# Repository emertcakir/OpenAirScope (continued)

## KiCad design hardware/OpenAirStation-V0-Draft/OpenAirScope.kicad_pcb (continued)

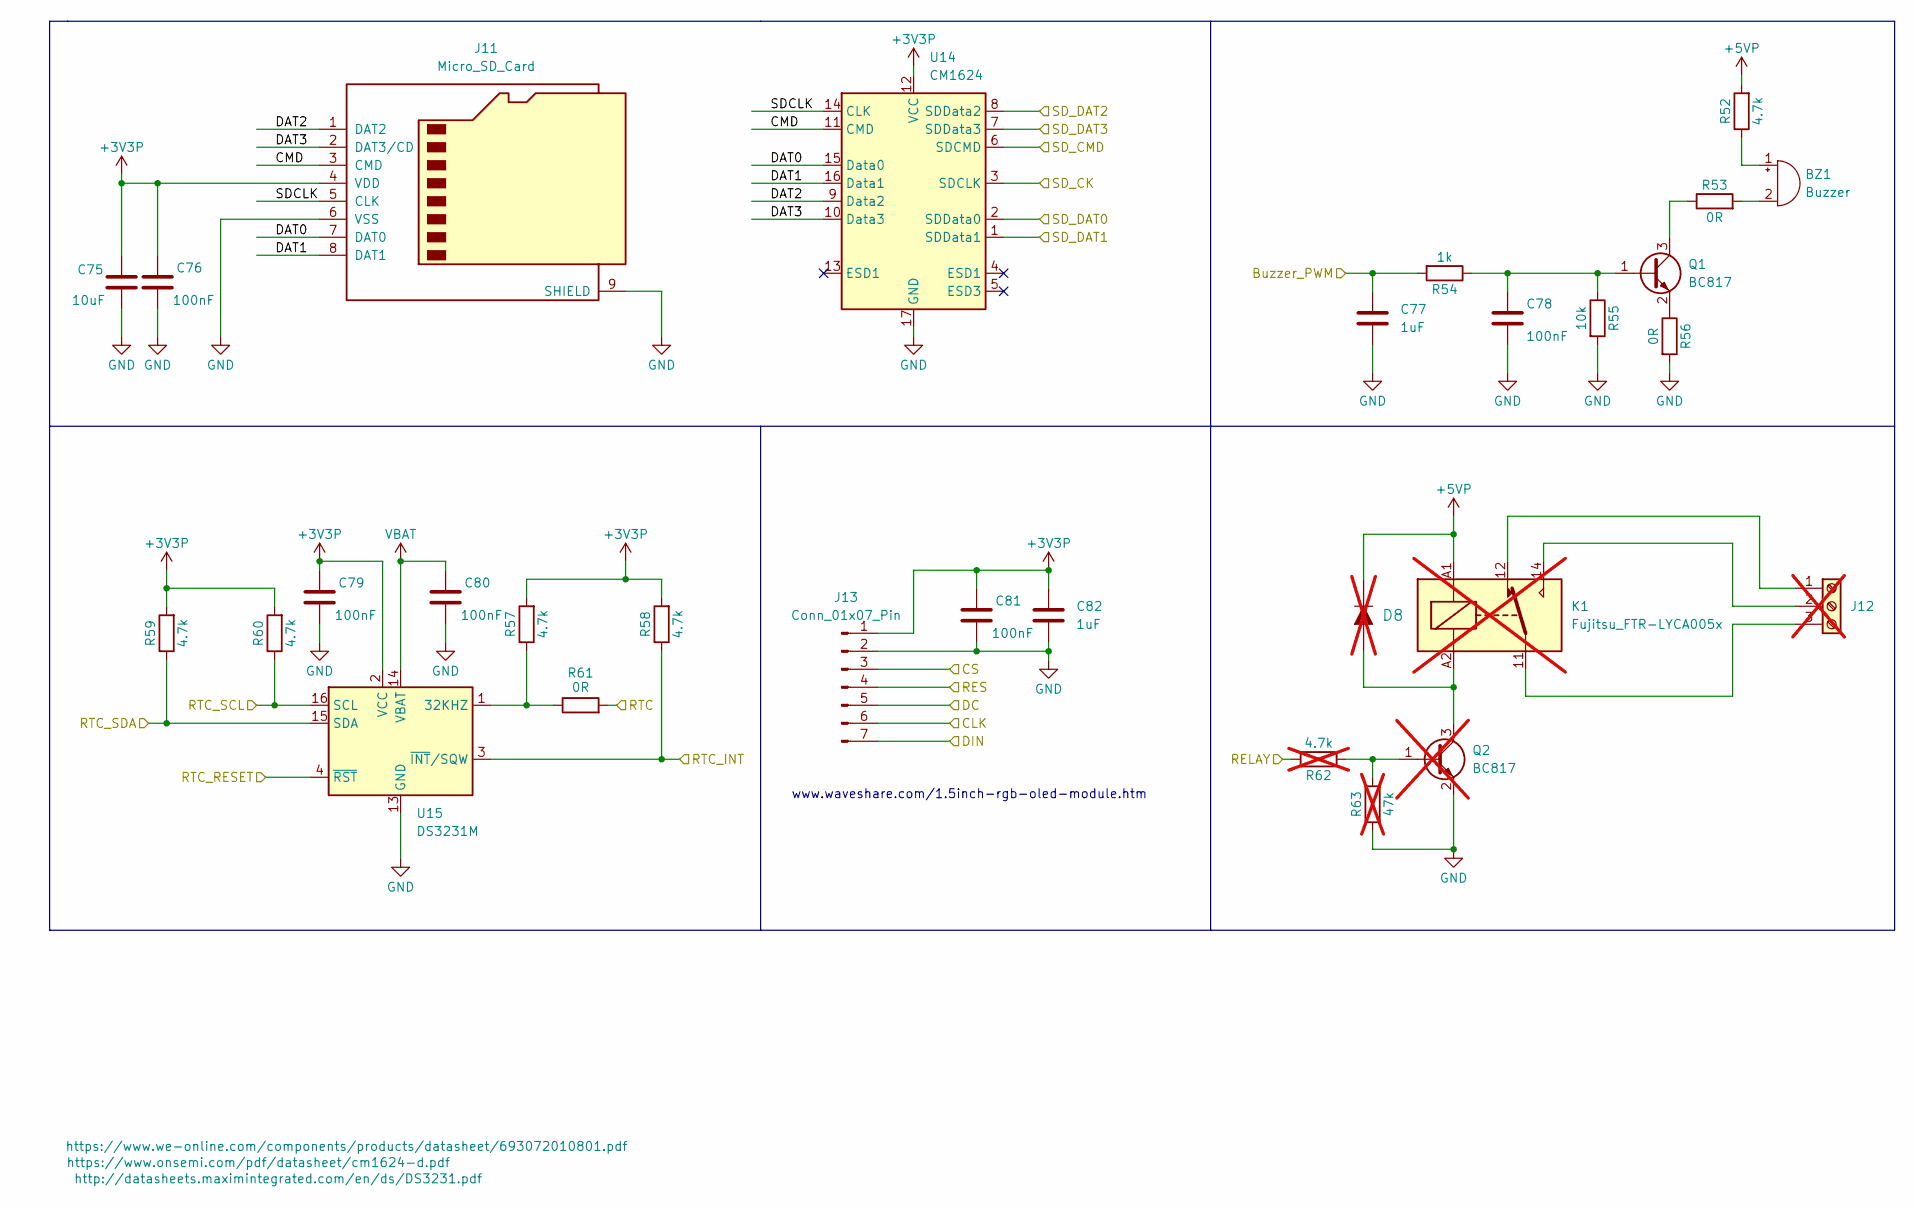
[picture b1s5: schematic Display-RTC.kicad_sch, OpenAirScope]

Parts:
BZ1: Buzzer; MagneticBuzzer_ProSignal_ABT-410-RC
C75: 10uF; C_0603_1608Metric
C76, C78, C79, C80, C81: 100nF; C_0603_1608Metric
C77, C82: 1uF; C_1206_3216Metric
D8: 1N4148W-TP; SOD-123; MPN 1N4148W-TP; Digi-Key_PN 1N4148WTPMSCT-ND; not fitted
J11: Micro_SD_Card; microSD_HC_Wuerth_693072010801
J12: Screw_Terminal_01x03; TerminalBlock_MetzConnect_Type059_RT06303HBWC_1x03_P3.50mm_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; not fitted
J13: Conn_01x07_Pin; PinHeader_1x07_P2.54mm_Vertical
K1: Fujitsu_FTR-LYCA005x; Relay_SPDT_Fujitsu_FTR-LYCA005x_FormC_Vertical; not fitted
Q1: BC817; SOT-23
Q2: BC817; SOT-23; not fitted
R52, R57, R58, R59, R60: 4.7k; R_0603_1608Metric
R53, R56, R61: 0R; R_0603_1608Metric
R54: 1k; R_0603_1608Metric
R55: 10k; R_0603_1608Metric
R62: 4.7k; R_0603_1608Metric; not fitted
R63: 47k; R_0603_1608Metric; not fitted
U14: CM1624; OnSemi_UDFN-16-1EP_1.35x3.3mm_P0.4mm_EP0.4x2.8mm
U15: DS3231M; SOIC-16W_7.5x10.3mm_P1.27mm

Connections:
+3V3P: C75.1, C76.1, C79.1, C81.1, C82.1, J11.4 (VDD), J13.1, R57.2, R58.2, R59.2, R60.2, U14.12 (VCC), U15.2 (VCC); also elsewhere on the board
+5VP: D8.K, K1.A1, R52.2; also elsewhere on the board
/Display-RTC/Buzzer_PWM: C77.1, R54.2; also elsewhere on the board
/Display-RTC/CLK: J13.6; also elsewhere on the board
/Display-RTC/CMD: J11.3 (CMD), U14.11 (CMD)
/Display-RTC/CS: J13.3; also elsewhere on the board
/Display-RTC/DAT0: J11.7 (DAT0), U14.15 (Data0)
/Display-RTC/DAT1: J11.8 (DAT1), U14.16 (Data1)
/Display-RTC/DAT2: J11.1 (DAT2), U14.9 (Data2)
/Display-RTC/DAT3: J11.2 (DAT3/CD), U14.10 (Data3)
/Display-RTC/DC: J13.5; also elsewhere on the board
/Display-RTC/DIN: J13.7; also elsewhere on the board
/Display-RTC/RES: J13.4; also elsewhere on the board
/Display-RTC/RTC: R61.2; also elsewhere on the board
/Display-RTC/RTC_INT: R58.1, U15.3 (~INT/SQW); also elsewhere on the board
/Display-RTC/RTC_RESET: U15.4 (~RST); also elsewhere on the board
/Display-RTC/RTC_SCL: R60.1, U15.16 (SCL); also elsewhere on the board
/Display-RTC/RTC_SDA: R59.1, U15.15 (SDA); also elsewhere on the board
/Display-RTC/SDCLK: J11.5 (CLK), U14.14 (CLK)
/Display-RTC/SD_CK: U14.3 (SDCLK); also elsewhere on the board
/Display-RTC/SD_CMD: U14.6 (SDCMD); also elsewhere on the board
/Display-RTC/SD_DAT0: U14.2 (SDData0); also elsewhere on the board
/Display-RTC/SD_DAT1: U14.1 (SDData1); also elsewhere on the board
/Display-RTC/SD_DAT2: U14.8 (SDData2); also elsewhere on the board
/Display-RTC/SD_DAT3: U14.7 (SDData3); also elsewhere on the board
GND: C75.2, C76.2, C77.2, C78.2, C79.2, C80.2, C81.2, C82.2, J11.6 (VSS), J11.9 (SHIELD), J13.2, Q2.2 (E), R55.2, R56.2, R63.1, U14.17 (GND), U15.5 (GND), U15.6 (GND), U15.7 (GND), U15.8 (GND), U15.9 (GND), U15.10 (GND), U15.11 (GND), U15.12 (GND), U15.13 (GND); also elsewhere on the board
unnamed: BZ1.1 (+), R52.1
unnamed: BZ1.2 (-), R53.2
unnamed: D8.A, K1.A2, Q2.3 (C)
unnamed: J12.1, K1.12
unnamed: J12.2, K1.14
unnamed: J12.3, K1.11
unnamed: C78.1, Q1.1 (B), R54.1, R55.1
unnamed: Q1.3 (C), R53.1
unnamed: Q1.2 (E), R56.1
unnamed: Q2.1 (B), R62.1, R63.2
unnamed: R57.1, R61.1, U15.1 (32KHZ)
VBAT: C80.1, U15.14 (VBAT); also elsewhere on the board

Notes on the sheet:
www.waveshare.com/1.5inch-rgb-oled-module.htm

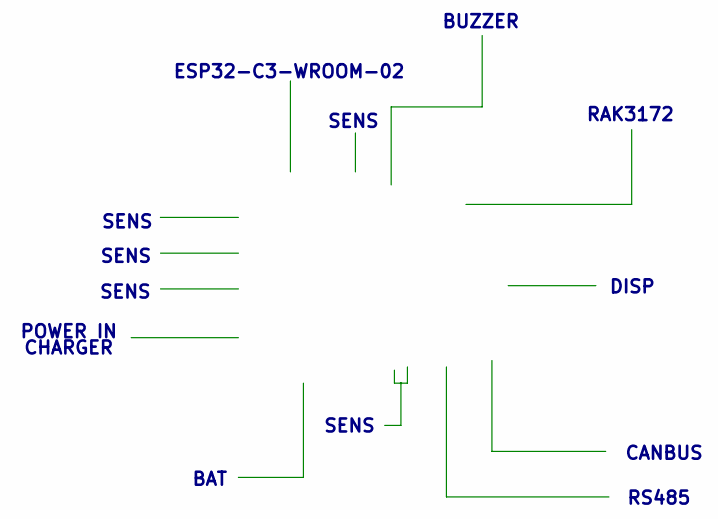
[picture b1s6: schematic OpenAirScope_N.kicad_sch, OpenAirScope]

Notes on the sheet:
CHARGER
DISP
SENS
BAT
ESP32-C3-WROOM-02
RAK3172
RS485
CANBUS
POWER IN
BUZZER

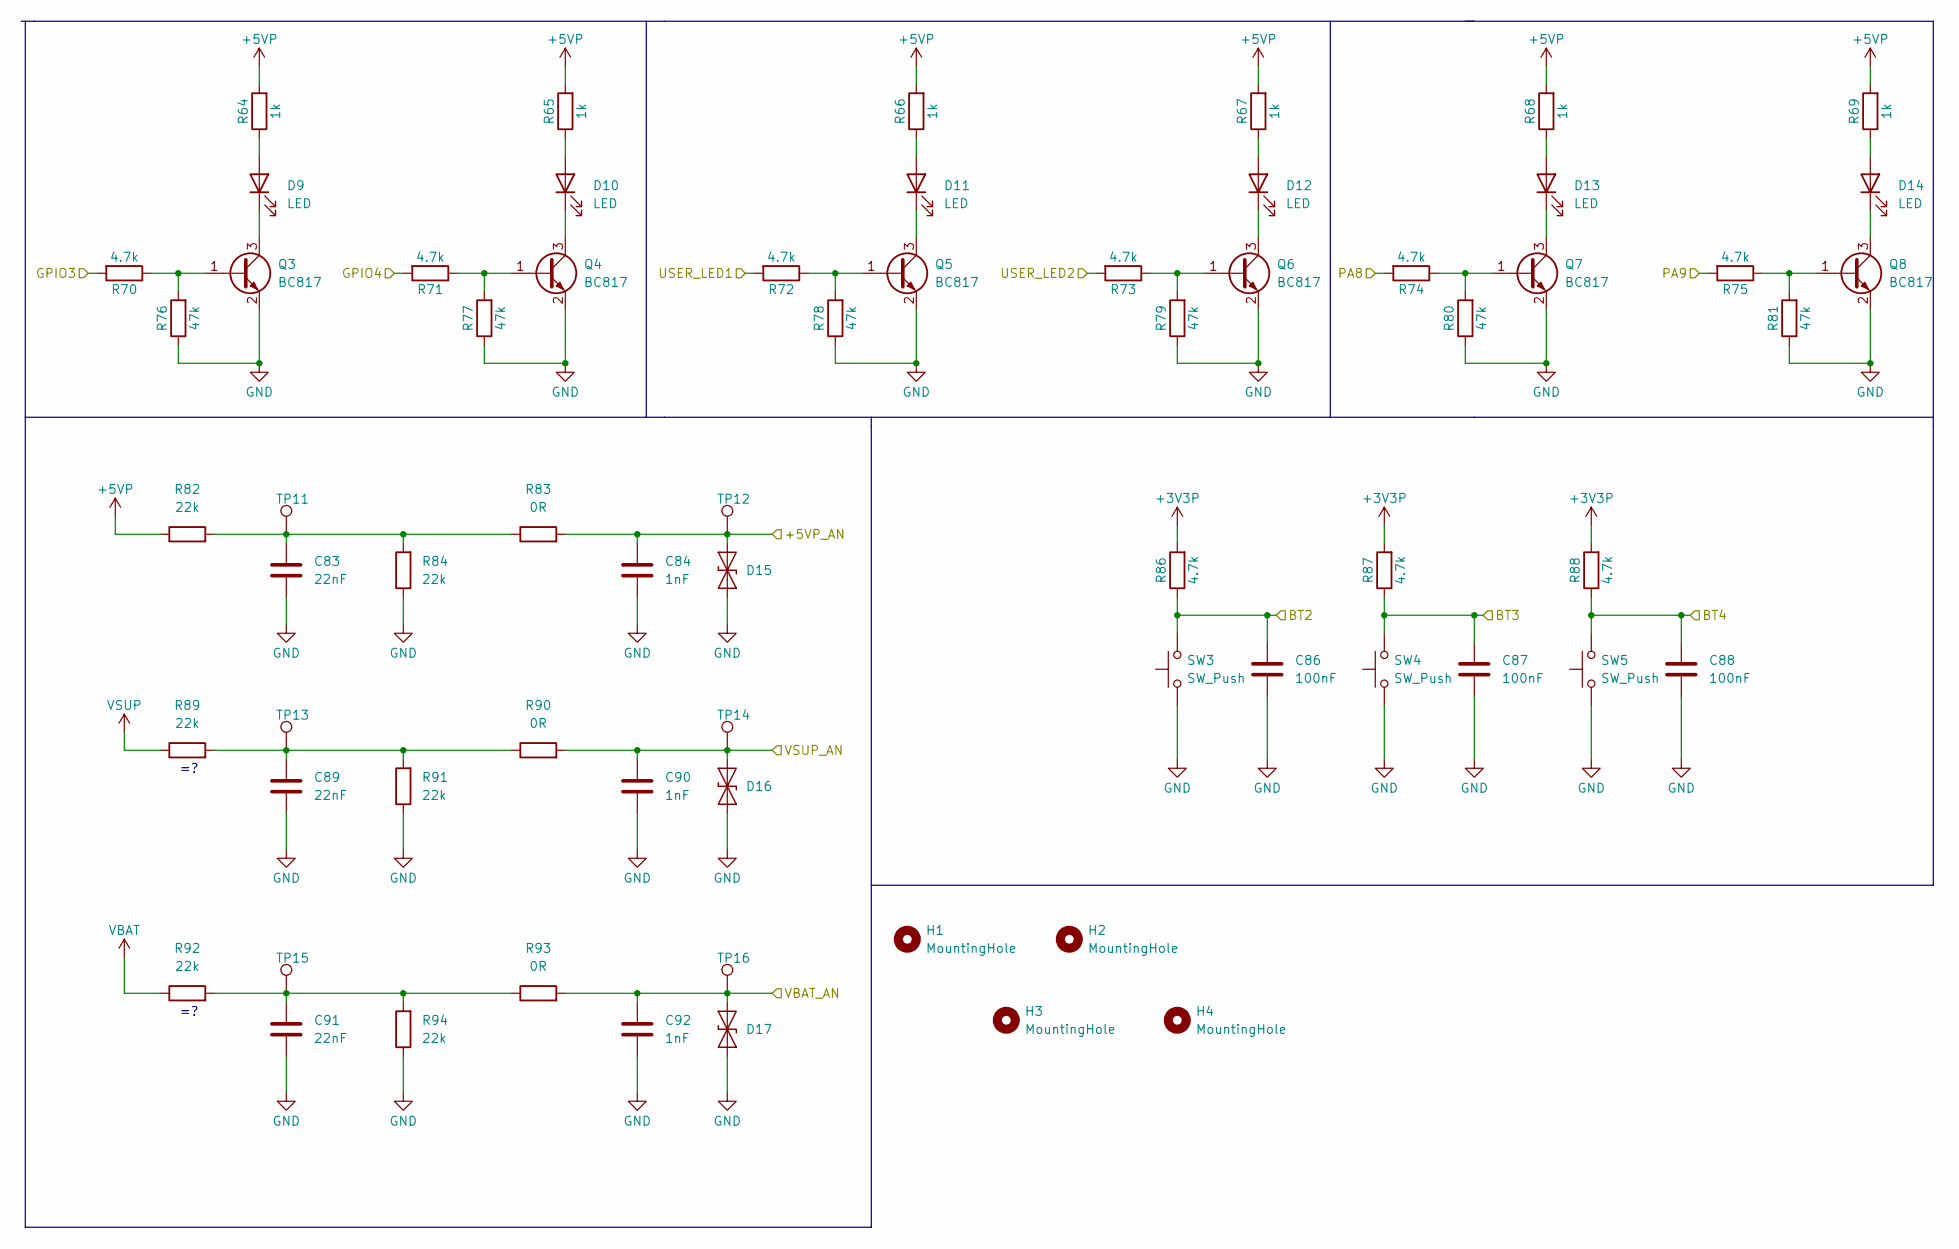
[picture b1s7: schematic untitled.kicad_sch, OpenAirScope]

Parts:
C83, C89, C91: 22nF; C_0603_1608Metric
C84, C90, C92: 1nF; C_0603_1608Metric
C86, C87, C88: 100nF; C_0603_1608Metric
D9, D10, D11, D12, D13, D14: LED; LED_0603_1608Metric
D15, D16, D17: ESD9B3.3ST5G; D_SOD-923
H1, H2, H3, H4: MountingHole; MountingHole_3.2mm_M3_ISO7380
Q3, Q4, Q5, Q6, Q7, Q8: BC817; SOT-23
R64, R65, R66, R67, R68, R69: 1k; R_0603_1608Metric
R70, R71, R72, R73, R74, R75, R86, R87, R88: 4.7k; R_0603_1608Metric
R76, R77, R78, R79, R80, R81: 47k; R_0603_1608Metric
R82, R84, R89, R91, R92, R94: 22k; R_0603_1608Metric
R83, R90, R93: 0R; R_0603_1608Metric
SW3, SW4, SW5: SW_Push; SW_PUSH_6mm_H13mm
TP11, TP12, TP13, TP14, TP15, TP16: TestPoint; TestPoint_Pad_D1.0mm

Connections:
+3V3P: R86.2, R87.2, R88.2; also elsewhere on the board
+5VP: R64.2, R65.2, R66.2, R67.2, R68.2, R69.2, R82.1; also elsewhere on the board
/Conn/GPIO3: R70.2; also elsewhere on the board
/Conn/GPIO4: R71.2; also elsewhere on the board
/Conn/PA8: R74.2; also elsewhere on the board
/Conn/PA9: R75.2; also elsewhere on the board
/Indicators/+5VP_AN: C84.1, D15.2 (A2), R83.2, TP12.1; also elsewhere on the board
/Indicators/BT2: C86.1, R86.1, SW3.2; also elsewhere on the board
/Indicators/BT3: C87.1, R87.1, SW4.2; also elsewhere on the board
/Indicators/BT4: C88.1, R88.1, SW5.2; also elsewhere on the board
/Indicators/USER_LED1: R72.2; also elsewhere on the board
/Indicators/USER_LED2: R73.2; also elsewhere on the board
/Indicators/VBAT_AN: C92.1, D17.2 (A2), R93.2, TP16.1; also elsewhere on the board
/Indicators/VSUP_AN: C90.1, D16.2 (A2), R90.2, TP14.1; also elsewhere on the board
GND: C83.2, C84.2, C86.2, C87.2, C88.2, C89.2, C90.2, C91.2, C92.2, D15.1 (A1), D16.1 (A1), D17.1 (A1), Q3.2 (E), Q4.2 (E), Q5.2 (E), Q6.2 (E), Q7.2 (E), Q8.2 (E), R76.1, R77.1, R78.1, R79.1, R80.1, R81.1, R84.1, R91.1, R94.1, SW3.1, SW4.1, SW5.1; also elsewhere on the board
unnamed: C83.1, R82.2, R83.1, R84.2, TP11.1
unnamed: C89.1, R89.2, R90.1, R91.2, TP13.1
unnamed: C91.1, R92.2, R93.1, R94.2, TP15.1
unnamed: D9.2 (A), R64.1
unnamed: D9.1 (K), Q3.3 (C)
unnamed: D10.2 (A), R65.1
unnamed: D10.1 (K), Q4.3 (C)
unnamed: D11.2 (A), R66.1
unnamed: D11.1 (K), Q5.3 (C)
unnamed: D12.2 (A), R67.1
unnamed: D12.1 (K), Q6.3 (C)
unnamed: D13.2 (A), R68.1
unnamed: D13.1 (K), Q7.3 (C)
unnamed: D14.2 (A), R69.1
unnamed: D14.1 (K), Q8.3 (C)
unnamed: Q3.1 (B), R70.1, R76.2
unnamed: Q4.1 (B), R71.1, R77.2
unnamed: Q5.1 (B), R72.1, R78.2
unnamed: Q6.1 (B), R73.1, R79.2
unnamed: Q7.1 (B), R74.1, R80.2
unnamed: Q8.1 (B), R75.1, R81.2
VBAT: R92.1; also elsewhere on the board
VSUP: R89.1; also elsewhere on the board

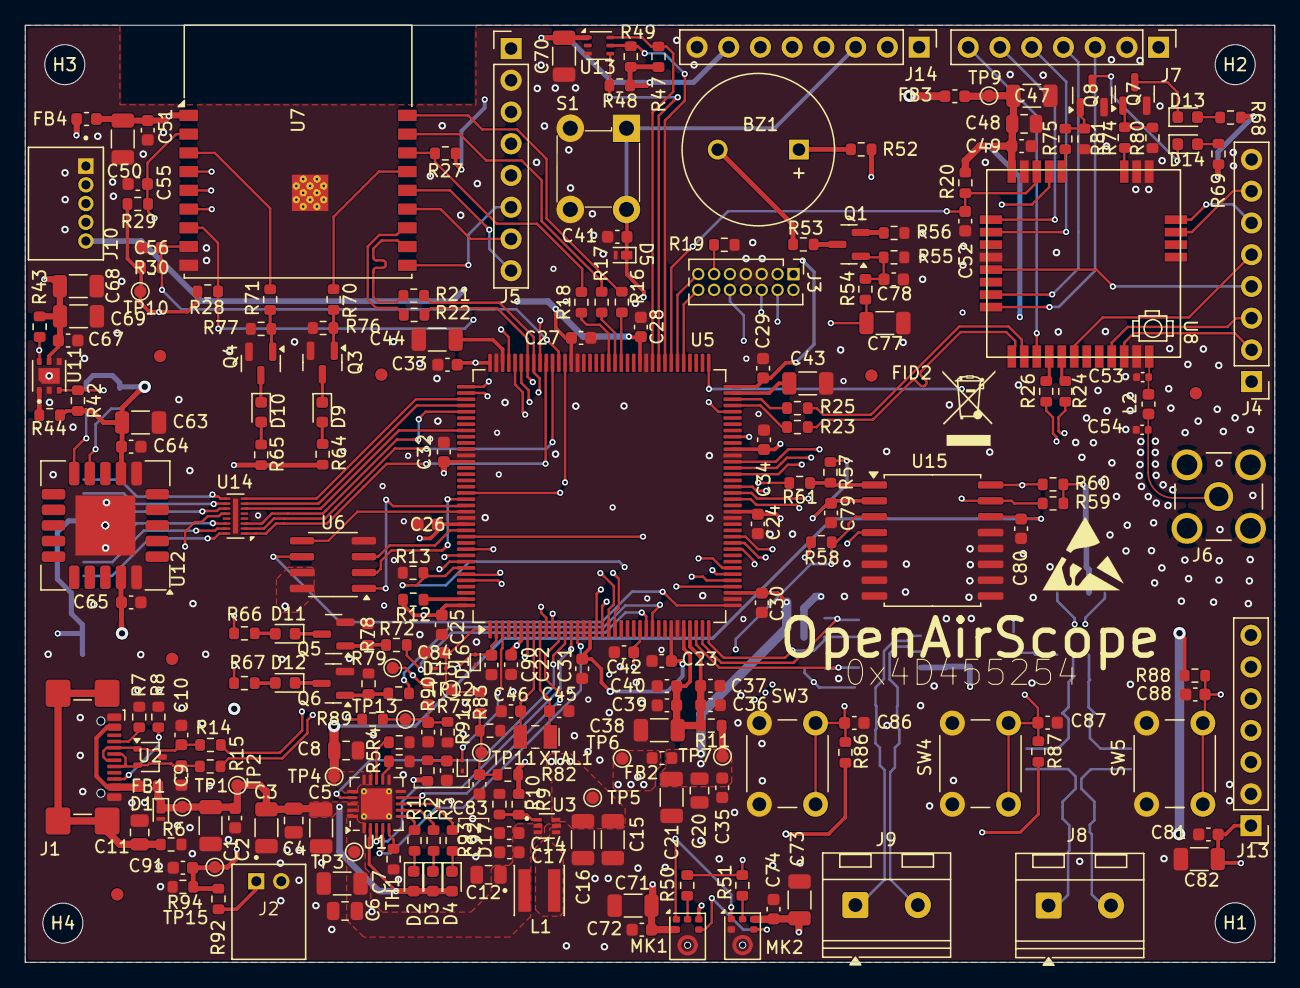
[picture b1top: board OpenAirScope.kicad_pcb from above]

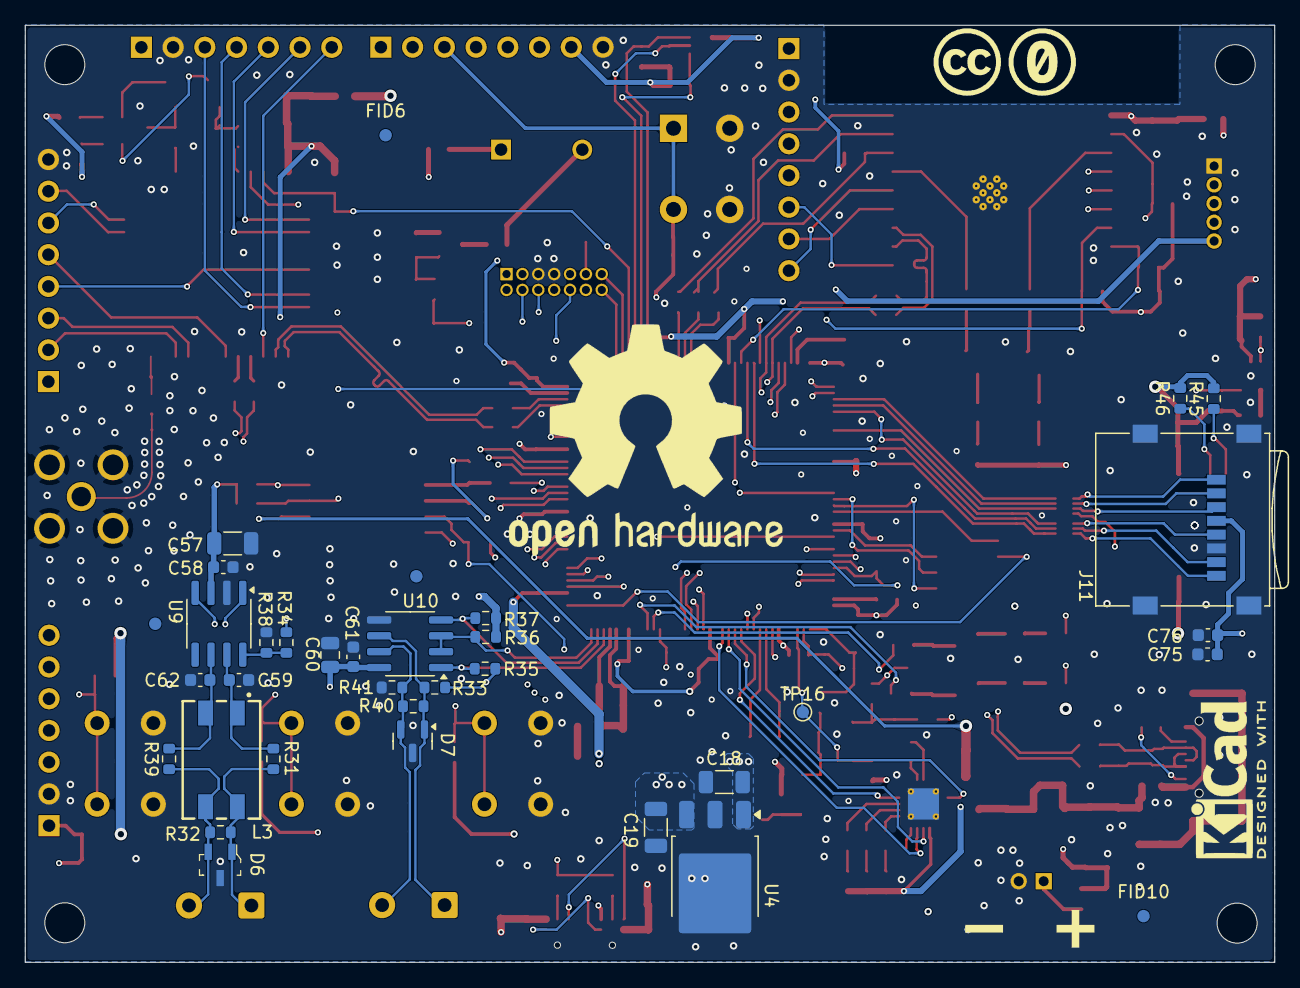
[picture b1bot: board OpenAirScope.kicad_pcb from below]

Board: 4 copper layers, 100.0 x 75.0 mm, 281 parts (38 on the bottom side), 184 nets.

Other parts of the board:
FID1, FID2, FID3, FID4, FID5, FID6, FID7, FID8, FID9, FID10: Fiducial; Fiducial_1mm_Mask2mm
l1: ESD-Logo_6.6x6mm_SilkScreen
l2: WEEE-Logo_4.2x6mm_SilkScreen
l3: OSHW-Logo2_24.3x20mm_SilkScreen
l4: KiCad-Logo2_5mm_SilkScreen
l5: Symbol_CreativeCommonsPublicDomain_SilkScreenTop_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; Symbol_CreativeCommonsPublicDomain_SilkScreenTop_Small

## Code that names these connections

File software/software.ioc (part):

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Mcu.Name=STM32H743ZITx
Mcu.Package=LQFP144
Mcu.UserName=STM32H743ZITx
PA0.Signal=UART4_TX
PA1.Signal=UART4_RX
PA10.Signal=USART1_RX
PA11.Signal=USB_OTG_FS_DM
PA12.Signal=USB_OTG_FS_DP
PA13\ (JTMS/SWDIO).Signal=DEBUG_JTMS-SWDIO
PA14\ (JTCK/SWCLK).Signal=DEBUG_JTCK-SWCLK
PA15\ (JTDI).Signal=DEBUG_JTDI
PA2.Signal=GPIO_Output
PA3.Signal=GPIO_Output
PA7.Signal=GPIO_Output
PA8.Signal=GPIO_Output
PA9.Signal=USART1_TX
PB0.Signal=GPIO_Output
PB1.Signal=GPIO_Output
PB10.Signal=USART3_TX
PB11.Signal=USART3_RX
PB12.Signal=GPIO_Output
PB2.Signal=GPIO_Output
PB3\ (JTDO/TRACESWO).Signal=DEBUG_JTDO-SWO
PB5.Signal=SPI1_MOSI
PB6.Signal=I2C1_SCL
PB7.Signal=I2C1_SDA
PB8.Mode=FDCAN_Activate
PB8.Signal=FDCAN1_RX
PB9.Mode=FDCAN_Activate
PB9.Signal=FDCAN1_TX
PC0.Signal=GPIO_Output
PC1.Signal=GPIO_Output
PC10.Signal=SDMMC1_D2
PC11.Signal=SDMMC1_D3
PC12.Signal=SDMMC1_CK
PC13.Signal=RTC_OUT_ALARM
PC6.Signal=S_TIM3_CH1
PC7.Signal=GPIO_Output
PC8.Signal=SDMMC1_D0
PC9.Signal=SDMMC1_D1
PD10.Signal=GPIO_Output
PD11.Signal=GPIO_Input
PD12.Signal=I2C4_SCL
PD13.Signal=I2C4_SDA
PD2.Signal=SDMMC1_CMD
PE11.Signal=S_TIM1_CH2
PE15.Signal=GPIO_Output
PE2.Signal=GPIO_Analog
PE3.Signal=GPIO_Analog
PE4.Signal=GPIO_Analog
PE7.Signal=GPIO_Input
PE8.Signal=GPIO_Input
PE9.Signal=GPIO_Input
PF0.Signal=I2C2_SDA
PF1.Signal=I2C2_SCL
PF2.Signal=GPIO_Output
PF3.Signal=GPIO_Output
PF4.Signal=GPIO_Output
PF5.Signal=GPIO_Output
PF6.Signal=UART7_RX
PF7.Signal=UART7_TX
PF8.Signal=GPIO_Input
PF9.Signal=GPIO_Input
PG0.Signal=GPIO_Output
PG1.Signal=GPIO_Input
PG11.Signal=SPI1_SCK
PG12.Signal=SPI6_MISO
PG13.Signal=SPI6_SCK
PG14.Signal=SPI6_MOSI
PG15.Signal=GPIO_Output
PG2.Signal=GPIO_Analog
PG3.Signal=GPIO_Output
PG4.Signal=GPIO_Output
RCC.SYSCLKFreq_VALUE=64000000
board=custom

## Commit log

2025-09-10 v0.1
2025-09-11 README.MD
2025-09-15 test
2025-11-19 v0.2
2026-06-14 v0.3
